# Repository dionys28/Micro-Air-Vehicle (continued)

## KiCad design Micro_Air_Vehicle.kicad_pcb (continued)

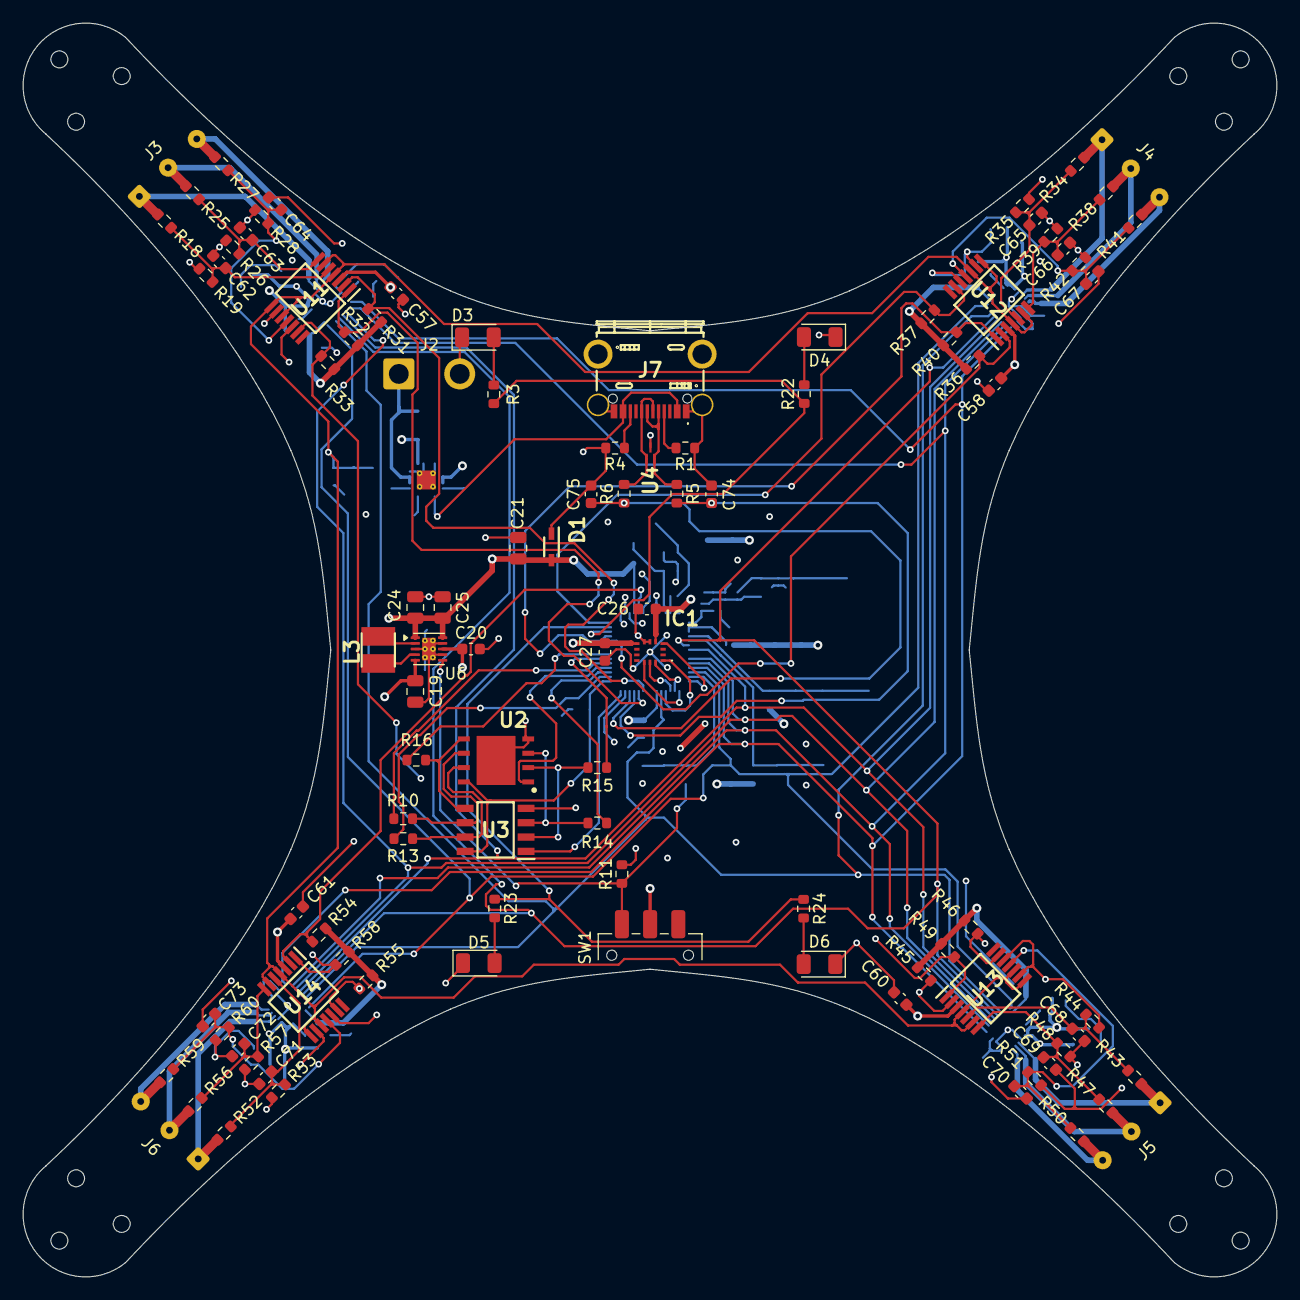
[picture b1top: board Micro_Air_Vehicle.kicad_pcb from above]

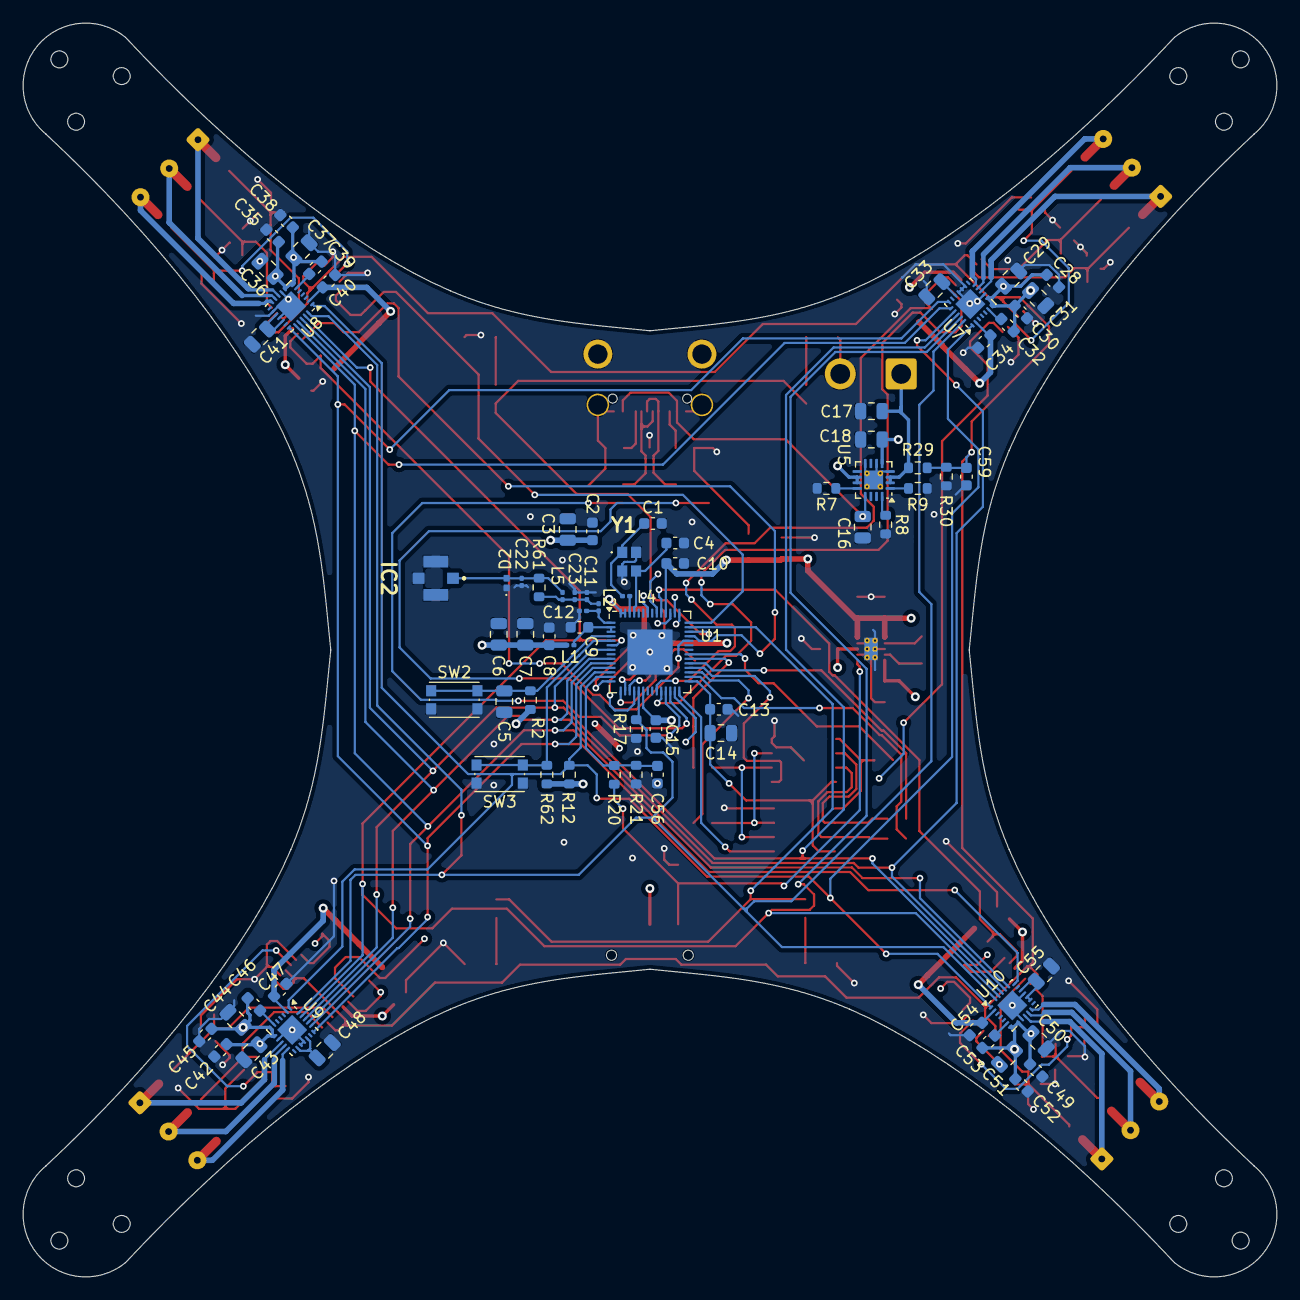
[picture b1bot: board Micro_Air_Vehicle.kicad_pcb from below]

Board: 4 copper layers, 111.1 x 111.1 mm, 174 parts (77 on the bottom side), 103 nets.

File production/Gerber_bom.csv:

Designator,Footprint,Quantity,Value,LCSC Part #
"C1, C4",0603,2,16pF,
"C10, C13, C15, C20, C26, C27, C28, C30, C32, C34, C35, C38, C39, C40, C42, C45, C46, C47, C49, C52, C53, C54, C56, C57, C58, C59, C60, C61, C8, C9",0603,30,100nF,
"C11, C12",0201,2,1.5pF,
"C14, C3, C33, C41, C48, C5, C55, C7",0805,8,1uF,
"C16, C17, C18, C19, C21, C24, C25, C29, C31, C36, C37, C43, C44, C50, C51, C6",0805,16,10uF,
C2,0603,1,10nF,
D1,Diode_D1,1,CPDV3V3A-HF,
D2,SVS03331P1RBQ.C,1,SVS03331P1RBQ.C,
D3,1206,1,LED_vorne_links,
D4,1206,1,LED_vorne_rechts,
D5,1206,1,LED_hinten_links,
D6,1206,1,LED_hinten_rechts,
IC1,BMI270,1,BMI270,
IC2,Antennen_Stecker,1,CONMHF1-SMD-G-T,
J2,SolderWire-1sqmm_1x02_P5.4mm_D1.4mm_OD2.7mm,1,Akku Stecker,
J3,SolderWire-0.1sqmm_1x03_P3.6mm_D0.4mm_OD1mm,1,Motor1,
J4,SolderWire-0.1sqmm_1x03_P3.6mm_D0.4mm_OD1mm,1,Motor2,
J5,SolderWire-0.1sqmm_1x03_P3.6mm_D0.4mm_OD1mm,1,Motor3,
J6,SolderWire-0.1sqmm_1x03_P3.6mm_D0.4mm_OD1mm,1,Motor4,
J7,USB480003A,1,USB4800-03-A,
"L1, L2",0201,2,2nH,
L3,Spule1.5uH,1,1.5uH,
L4,0201,1,24nH,
"R1, R4",0603,2,5.1k,
"R10, R13, R14, R15, R16, R61",0603,6,0R,
"R11, R17, R20, R21",0603,4,100k,
R12,0603,1,5k1,
"R18, R19, R25, R26, R27, R28, R34, R35, R38, R39, R41, R42, R43, R44, R47, R48, R50, R51, R52, R53, R56, R57, R59, R60",0603,24,22k,
"R2, R30, R31, R32, R33, R36, R37, R40, R45, R46, R49, R54, R55, R58, R62, R9",0603,16,10k,
"R22, R23, R24, R3",0603,4,330R,
R29,0603,1,30k,
"R5, R6",0603,2,22,
R7,0603,1,3k1,
R8,0603,1,3k,
SW1,SW_SPDT_CK_JS102011SAQN,1,SW_SPDT,
"SW2, SW3",SW_Push_1P1T_NO_CK_KMR2,2,SW_Push,
U1,QFN-56-1EP_7x7mm_P0.4mm_EP4x4mm,1,ESP32-S3,
"U10, U7, U8, U9",Texas_RRW0024A_WQFN-24-1EP_3x3mm_P0.4mm_EP1.9x1.9mm,4,DRV8311P,
"U11, U12, U13, U14",LMV339IPWR,4,LMV339,
U2,FLASH,1,FLASH,
U3,PSRAM,1,PSRAM,
U4,TPD2EUSB30ADRTR,1,TPD2EUSB30A,
U5,VQFN-16-1EP_3x3mm_P0.5mm_EP1.68x1.68mm_ThermalVias,1,BQ24074RGT,
U6,WSON-10-1EP_2.5x2.5mm_P0.5mm_EP1.2x2mm_ThermalVias,1,TPS63031DSK,
Y1,40MHz_Quarz,1,40MHz Quarz,
